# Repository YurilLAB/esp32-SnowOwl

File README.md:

<div align="center">

# 🦉 ESP32-SnowOwl

**A multi-purpose wireless _offensive &amp; defensive_ security multitool.**

Three processors — **ESP32-S3 + ESP32-C5 (5 GHz Wi‑Fi) + ARM Linux** — driving a wall of radios and readers: dual‑band Wi‑Fi, BLE, 2.4 GHz, Sub‑GHz, **LoRa**, IR, **NFC**, **125 kHz RFID**, **iButton** &amp; GPS, in one stackable handheld.

</div>

> ⚠️ **Authorized use only.** SnowOwl is built for security research, education, CTFs, and testing on systems you own or are explicitly authorized to assess. You are solely responsible for complying with all applicable laws and regulations.

---

## 📖 About

**ESP32-SnowOwl** is a hardware evolution of [CiferTech's **ESP32‑DIV**](https://github.com/cifertech/ESP32-DIV) — the open-source ESP32‑S3 wireless multitool. SnowOwl keeps the entire ESP32‑DIV toolset and then piles on the compute, radios and readers the stock board doesn't have.

**Three processors, each doing what it's best at:**

- 🦅 **ESP32‑S3 — the controller.** The base ESP32‑DIV brain: the on‑device UI, 2.4 GHz Wi‑Fi &amp; BLE, and orchestration of every radio.
- 📡 **ESP32‑C5 — the 5 GHz reach.** A dual‑band **Wi‑Fi 6 (2.4 + 5 GHz)** co‑processor that adds the entire **5 GHz** band the S3 can't touch, on its own antenna and its own regulated rail.
- 🐧 **RV1106 ARM Linux — the analyst.** A real Linux computer (Luckfox Core1106) for capture, monitoring, scripting and heavy on‑device tooling — self‑powered from **its own USB‑C**.

Offense on the talons, analysis in the eyes. Silent, patient, built for the dark — the snow owl fits.

---

## 🦉 What SnowOwl adds over ESP32‑DIV

| Addition | Part | What it brings |
|---|---|---|
| 📡 **5 GHz Wi‑Fi co‑processor** | ESP32‑C5‑WROOM‑1U | Dual‑band **Wi‑Fi 6 (2.4 + 5 GHz)** — the 5 GHz band the ESP32‑S3 can't reach. Own U.FL antenna, own AP7361C LDO rail, UART‑linked to the S3. |
| 🐧 **ARM Linux co‑processor** | Luckfox RV1106 (Core1106) | A genuine Linux computer on the shield for capture, monitoring and heavy tooling. Self‑powered from **its own USB‑C**. |
| 🧲 **NFC** (13.56 MHz) | PN532 | Read / emulate / relay over a **dedicated I²C bus** owned by the S3 — independent of the radios. |
| 📇 **125 kHz LF RFID** | HTRC110 + coil | Low‑frequency prox‑card read &amp; emulation (EM4100‑class) — a band the stock board lacks. |
| 🔑 **iButton / 1‑Wire** | 1‑Wire header | Dallas iButton + 1‑Wire contact interface. |
| 📻 **LoRa / long‑range Sub‑GHz** | SX1262 (+ Johanson match) | Long‑range LoRa &amp; FSK on Sub‑GHz, alongside the OOK/ASK radios. |
| 📻 **High‑performance Sub‑GHz** | CC1200 | A higher‑performance Sub‑GHz transceiver in addition to the classic CC1101. |
| 💾 **External flash** | W25Q128 (16 MB) | Non‑volatile storage for captures, logs and dumps. |
| 🧱 **4‑layer, power‑hardened PCB** | — | Dedicated **GND** and **3V3** planes, per‑rail decoupling and bulk caps for clean RF and stable multi‑radio operation. |

---

## 🎯 Features

SnowOwl runs the full **ESP32‑DIV** firmware feature set on the ESP32‑S3, extended with the SnowOwl radios and readers. Capabilities by band:

### 📡 Wi‑Fi — 2.4 GHz (ESP32‑S3) **+ 5 GHz (ESP32‑C5)** · **5 GHz is NEW**
| Capability | Notes |
|---|---|
| Dual‑band recon &amp; scanning | AP / station discovery across **2.4 *and* 5 GHz**, channels, RSSI |
| Deauth / attack testing | Targeted &amp; broadcast frame testing, now on 5 GHz networks too |
| Beacon / probe flooding | SSID beacon spam, probe generation |
| Packet monitor / capture | Sniffing, with hand‑off to the ARM side for storage &amp; analysis |
| Evil‑portal / captive testing | Rogue‑AP and captive‑portal workflows |

### 🔵 Bluetooth / BLE
| Capability | Notes |
|---|---|
| BLE scan &amp; recon | Device discovery, service enumeration |
| Advertising / spam | BLE advertisement flooding &amp; spoofing |
| Proximity‑pairing tests | Device‑spam nuisance testing |

### 📶 2.4 GHz / nRF24 (3× nRF24L01+)
| Capability | Notes |
|---|---|
| Channel scanner / analyzer | 2.4 GHz spectrum sweep across three radios |
| Multi‑channel jamming (test) | Wide/targeted 2.4 GHz interference testing |

### 📻 Sub‑GHz — CC1101 · CC1200 · **SX1262 LoRa**
| Capability | Notes |
|---|---|
| Scan &amp; frequency analysis | RSSI sweep, signal hunting |
| Capture / replay | Record &amp; re‑transmit OOK/ASK signals |
| **LoRa / long‑range** | SX1262 for LoRa &amp; long‑range FSK |
| Jamming (test) | Sub‑GHz interference testing |

### 📺 Infrared (TSOP1838 RX + IR TX)
| Capability | Notes |
|---|---|
| Receive / decode | Capture IR remotes |
| Send / replay | Transmit stored or brute‑forced codes |

### 🧲 NFC / RFID — 13.56 MHz (PN532)
| Capability | Notes |
|---|---|
| Read / dump | MIFARE‑class tags &amp; UIDs |
| Emulate / relay | Card emulation and relay over the dedicated I²C bus |

### 📇 LF RFID — 125 kHz (HTRC110) &amp; 🔑 iButton · **NEW**
| Capability | Notes |
|---|---|
| 125 kHz read / emulate | EM4100‑class prox cards |
| iButton / 1‑Wire | Dallas contact keys |

### 🛰️ GPS (NEO‑M9N)
| Capability | Notes |
|---|---|
| Location &amp; time | Fix, NMEA, wardriving support |

### 🐧 ARM Linux co‑processor (RV1106) · **NEW**
| Capability | Notes |
|---|---|
| On‑device capture &amp; storage | Long‑running packet/loot capture without a laptop, to the 16 MB flash / SD |
| Monitoring / blue‑team | Run standard Linux security &amp; monitoring tooling on‑device |
| Scripting &amp; automation | Python/shell orchestration of the S3 &amp; C5 radios |

### 🧰 Device &amp; System
| Capability | Notes |
|---|---|
| Display UI | On‑device menu on the ESP32‑DIV TFT |
| Storage | microSD + **16 MB external flash** |
| Settings | Per‑module configuration |

> The exact per‑tool menu is inherited from the ESP32‑DIV firmware — see the [ESP32‑DIV wiki](https://github.com/cifertech/ESP32-DIV/wiki) for the full tool list.

---

## 🔧 Hardware Overview

### 🧠 Compute
- **ESP32‑S3** — application processor, 2.4 GHz Wi‑Fi &amp; BLE, UI (on the main board)
- **ESP32‑C5‑WROOM‑1U** — dual‑band **2.4 / 5 GHz Wi‑Fi 6** co‑processor (U.FL antenna, AP7361C LDO rail, UART link)
- **Luckfox RV1106 (Core1106)** — ARM Linux SoM, self‑powered via its **own USB‑C**

### 📡 Radios
- **3× nRF24L01+** — 2.4 GHz
- **CC1101** + **CC1200** — Sub‑GHz transceivers
- **SX1262** (+ Johanson integrated match) — LoRa / long‑range Sub‑GHz
- **7× SMA** antenna ports + U.FL

### 🧲 Readers &amp; sensors
- **PN532** — 13.56 MHz NFC (dedicated I²C bus, 27.12 MHz)
- **HTRC110** + coil — 125 kHz LF RFID
- **iButton / 1‑Wire** contact interface
- **TSOP1838** IR receiver + IR transmit
- **NEO‑M9N** — GPS

### 🔌 Power, storage &amp; protection
- **W25Q128** — 16 MB SPI flash
- microSD
- **AP7361C‑3.3** LDO (C5 rail), dedicated USB‑C for the ARM SoM
- **USBLC6‑2SC6** USB ESD protection, **SN74LVC2G34** level buffer
- Power hardening: bulk + per‑rail decoupling capacitors

Mates to the main board through the existing 20‑pin stack header; pogo/standoff holes are kept clear for a flat stack.

---

## 🧱 PCB / Manufacturing

- Designed in **KiCad 10**.
- **4‑layer stackup** — `F.Cu (signal) · In1 (GND plane) · In2 (3V3 plane) · B.Cu (signal)` for clean RF return paths and a quiet supply.
- Power‑planned per the datasheets of each part (per‑rail decoupling + bulk); RF nets use integrated matching where the transceiver vendors provide it.
- Intended for standard 4‑layer fabrication (e.g. JLCPCB); the 4‑layer option adds only a few dollars per unit over 2‑layer.

> **Status:** hardware design in active development. Placement and power are complete; signal routing is being finished. Renders and design notes live in [`/hardware`](hardware).

---

## ⚠️ Legal &amp; Responsible Use

SnowOwl is an **offensive *and* defensive** research platform. It is intended **only** for:

- testing systems you **own** or are **explicitly authorized** to assess,
- security education, CTFs, and lab research,
- defensive monitoring and blue‑team work.

Do **not** use it to access, disrupt, or interfere with networks, devices, cards, or systems you do not own or lack permission to test. Radio transmission is regulated — respect your local RF laws and licensed bands. **You** are responsible for how you use this tool.

---

## 📜 License

Released under the **MIT License** — see [`LICENSE`](LICENSE).

SnowOwl is a derivative of **ESP32‑DIV** (© CiferTech, MIT). The original work's terms are honored and its authors are credited below.

---

## 🙌 Credits

- **[CiferTech](https://github.com/cifertech)** — the original [ESP32‑DIV](https://github.com/cifertech/ESP32-DIV) platform and firmware that SnowOwl builds on. 🙏
- **YurilLAB** — SnowOwl hardware: the 5 GHz Wi‑Fi + ARM‑Linux compute, the NFC / 125 kHz RFID / iButton / LoRa additions, power hardening, and the 4‑layer redesign.

---

## 💬 Contributing &amp; Support

Issues, ideas, and pull requests are welcome. If SnowOwl is useful to you, a ⭐ helps.

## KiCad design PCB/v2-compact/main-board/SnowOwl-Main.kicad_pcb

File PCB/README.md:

# 🦉 SnowOwl — PCB

**Clean slate.** All previous CAD — boards, schematics, footprints, floorplan and renders — has
been wiped. The hardware direction is changing and the design is being started over from scratch.

```
PCB/
└── RESEARCH.md    ← component & schematic reference carried over from the old attempt
```

## RESEARCH.md

The only thing kept: the electrical research worth not repeating.

- **System architecture** — which processor owns what, and the SPI-spine approach.
- **Component inventory** — every radio/reader, and which ones are self-contained modules vs.
  chip-down parts that need a crystal and an RF front-end.
- **Power** — the single-USB-C / battery topology, plus **datasheet pinout corrections** for the
  charger, regulators and fuel gauge (the old symbols had invented pinouts).
- **RF front-end topologies** — matching + filter chains for the chip-down radios, with the
  caveat that every L/C value still needs VNA tuning.
- **Schematic gotchas** — including the net-merge bug that silently shorted whole nets twice.

It deliberately assumes **no particular board size, layout or form factor**, so none of it
constrains the new design.

> Fabrication outputs (`gerbers-out/`, zips) are git-ignored.

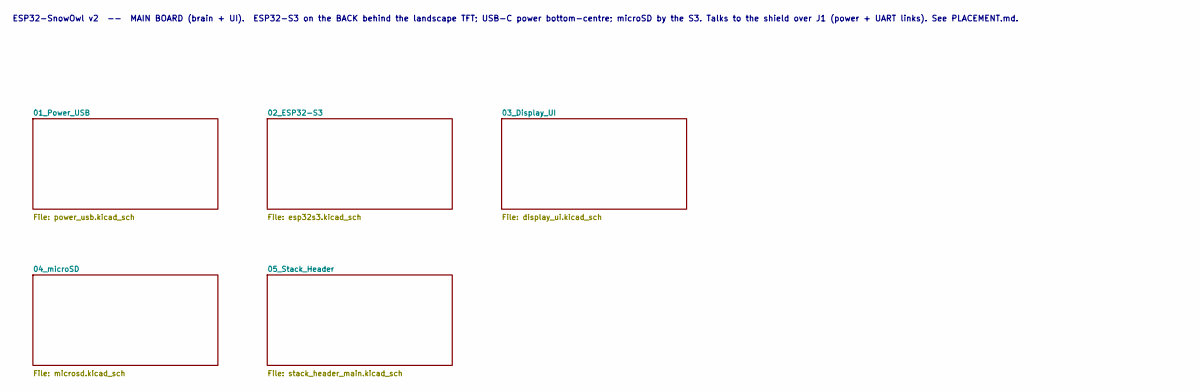
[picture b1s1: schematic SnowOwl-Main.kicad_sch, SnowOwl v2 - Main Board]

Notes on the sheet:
ESP32-SnowOwl v2 -- MAIN BOARD (brain + UI). ESP32-S3 on the BACK behind the landscape TFT; USB-C power bottom-centre; microSD by the S3. Talks to the shield over J1 (power + UART links). See PLACEMENT.md.

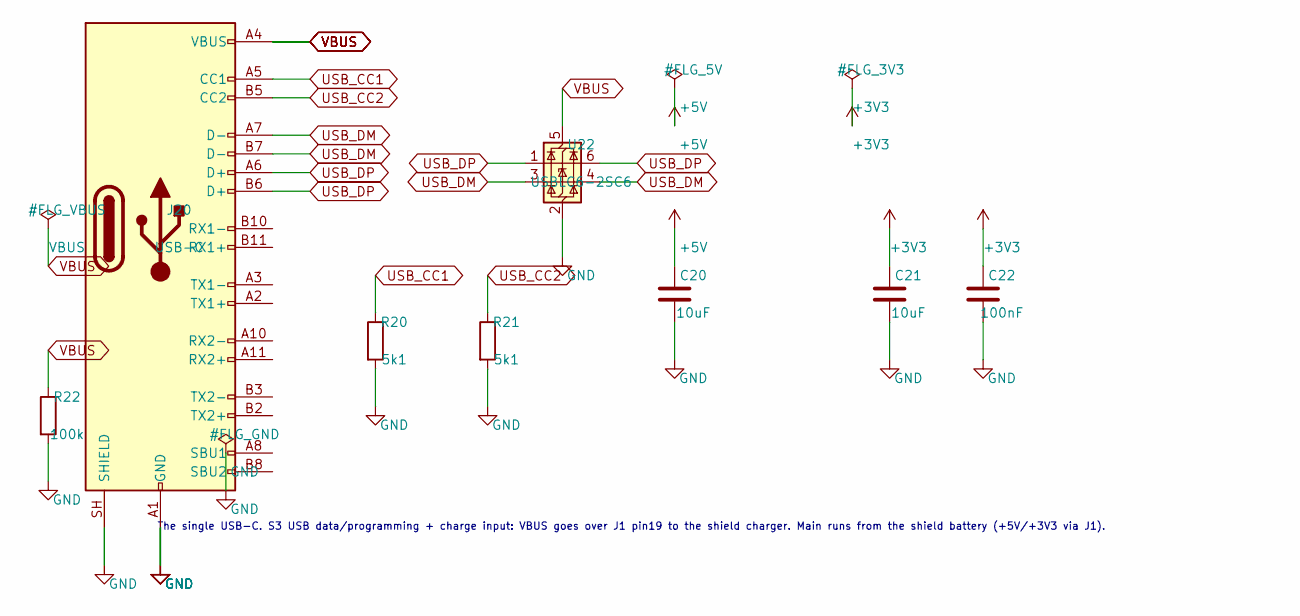
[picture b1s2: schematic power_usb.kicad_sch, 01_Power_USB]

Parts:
C20, C21: 10uF; C_0402_1005Metric
C22: 100nF; C_0402_1005Metric
J20: USB-C; USB_C_Receptacle_HRO_TYPE-C-31-M-12
R20, R21: 5k1; R_0402_1005Metric
R22: 100k; R_0402_1005Metric
U22: USBLC6-2SC6; SOT-23-6

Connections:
+3V3: C21.1, C22.1; also elsewhere on the board
+5V: C20.1; also elsewhere on the board
GND: C20.2, C21.2, C22.2, J20.A1 (GND), J20.A12 (GND), J20.B1 (GND), J20.B12 (GND), J20.SH (SHIELD), R20.2, R21.2, R22.2, U22.2 (GND); also elsewhere on the board
USB_CC1: J20.A5 (CC1), R20.1
USB_CC2: J20.B5 (CC2), R21.1
USB_DM: J20.A7 (D-), J20.B7 (D-), U22.3 (I/O2), U22.4 (I/O2); also elsewhere on the board
USB_DP: J20.A6 (D+), J20.B6 (D+), U22.1 (I/O1), U22.6 (I/O1); also elsewhere on the board
VBUS: J20.A4 (VBUS), J20.A9 (VBUS), J20.B4 (VBUS), J20.B9 (VBUS), R22.1, U22.5 (VBUS); also elsewhere on the board

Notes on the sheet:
The single USB-C. S3 USB data/programming + charge input: VBUS goes over J1 pin19 to the shield charger. Main runs from the shield battery (+5V/+3V3 via J1).

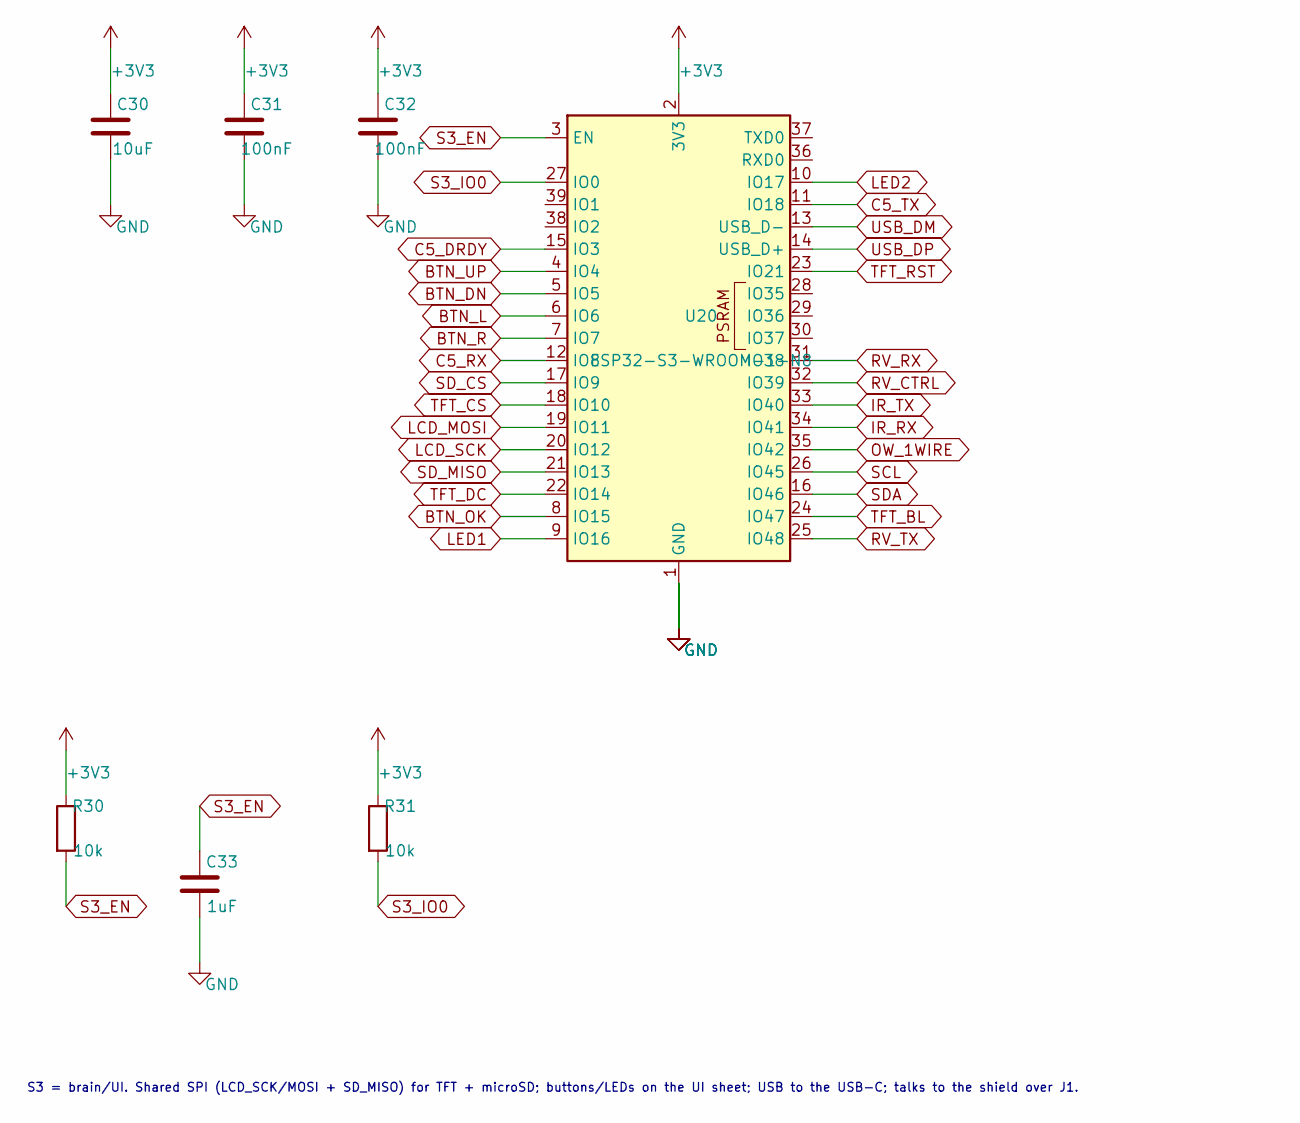
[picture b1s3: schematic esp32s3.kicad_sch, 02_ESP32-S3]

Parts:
C30: 10uF; C_0402_1005Metric
C31, C32: 100nF; C_0402_1005Metric
C33: 1uF; C_0402_1005Metric
R30, R31: 10k; R_0402_1005Metric
U20: ESP32-S3-WROOM-1-N8; ESP32-S3-WROOM-1

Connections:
+3V3: C30.1, C31.1, C32.1, R30.1, R31.1, U20.2 (3V3); also elsewhere on the board
BTN_DN: U20.5 (IO5); also elsewhere on the board
BTN_L: U20.6 (IO6); also elsewhere on the board
BTN_OK: U20.8 (IO15); also elsewhere on the board
BTN_R: U20.7 (IO7); also elsewhere on the board
BTN_UP: U20.4 (IO4); also elsewhere on the board
C5_DRDY: U20.15 (IO3); also elsewhere on the board
C5_RX: U20.12 (IO8); also elsewhere on the board
C5_TX: U20.11 (IO18); also elsewhere on the board
GND: C30.2, C31.2, C32.2, C33.2, U20.1 (GND), U20.40 (GND), U20.41 (GND); also elsewhere on the board
IR_RX: U20.34 (IO41); also elsewhere on the board
IR_TX: U20.33 (IO40); also elsewhere on the board
LCD_MOSI: U20.19 (IO11); also elsewhere on the board
LCD_SCK: U20.20 (IO12); also elsewhere on the board
LED1: U20.9 (IO16); also elsewhere on the board
LED2: U20.10 (IO17); also elsewhere on the board
OW_1WIRE: U20.35 (IO42); also elsewhere on the board
RV_CTRL: U20.32 (IO39); also elsewhere on the board
RV_RX: U20.31 (IO38); also elsewhere on the board
RV_TX: U20.25 (IO48); also elsewhere on the board
S3_EN: C33.1, R30.2, U20.3 (EN)
S3_IO0: R31.2, U20.27 (IO0)
SCL: U20.26 (IO45); also elsewhere on the board
SDA: U20.16 (IO46); also elsewhere on the board
SD_CS: U20.17 (IO9); also elsewhere on the board
SD_MISO: U20.21 (IO13); also elsewhere on the board
TFT_BL: U20.24 (IO47); also elsewhere on the board
TFT_CS: U20.18 (IO10); also elsewhere on the board
TFT_DC: U20.22 (IO14); also elsewhere on the board
TFT_RST: U20.23 (IO21); also elsewhere on the board
USB_DM: U20.13 (USB_D-); also elsewhere on the board
USB_DP: U20.14 (USB_D+); also elsewhere on the board

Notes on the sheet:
S3 = brain/UI. Shared SPI (LCD_SCK/MOSI + SD_MISO) for TFT + microSD; buttons/LEDs on the UI sheet; USB to the USB-C; talks to the shield over J1.

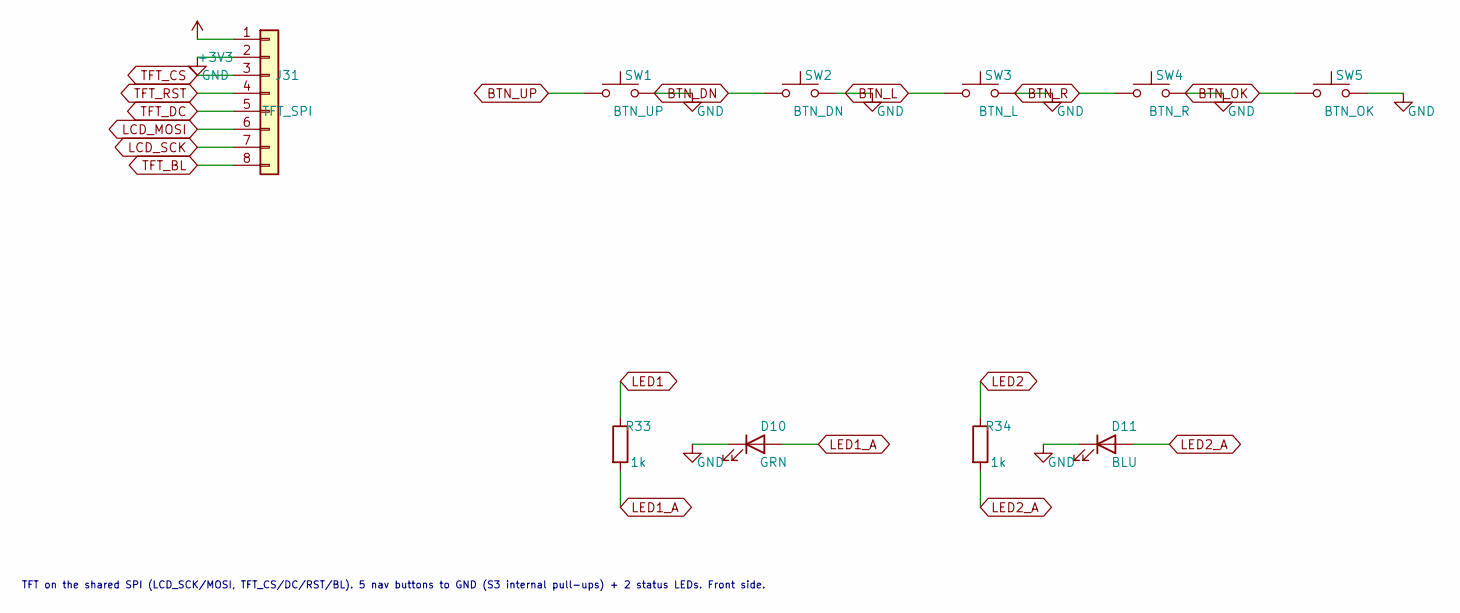
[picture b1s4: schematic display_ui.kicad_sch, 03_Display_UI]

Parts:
D10: GRN; LED_0805_2012Metric
D11: BLU; LED_0805_2012Metric
J31: TFT_SPI; PinHeader_1x08_P2.54mm_Vertical
R33, R34: 1k; R_0402_1005Metric
SW1: BTN_UP; SW_PUSH_6mm
SW2: BTN_DN; SW_PUSH_6mm
SW3: BTN_L; SW_PUSH_6mm
SW4: BTN_R; SW_PUSH_6mm
SW5: BTN_OK; SW_PUSH_6mm

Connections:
+3V3: J31.1; also elsewhere on the board
BTN_DN: SW2.1; also elsewhere on the board
BTN_L: SW3.1; also elsewhere on the board
BTN_OK: SW5.1; also elsewhere on the board
BTN_R: SW4.1; also elsewhere on the board
BTN_UP: SW1.1; also elsewhere on the board
GND: D10.1 (K), D11.1 (K), J31.2, SW1.2, SW2.2, SW3.2, SW4.2, SW5.2; also elsewhere on the board
LCD_MOSI: J31.6; also elsewhere on the board
LCD_SCK: J31.7; also elsewhere on the board
LED1: R33.1; also elsewhere on the board
LED1_A: D10.2 (A), R33.2
LED2: R34.1; also elsewhere on the board
LED2_A: D11.2 (A), R34.2
TFT_BL: J31.8; also elsewhere on the board
TFT_CS: J31.3; also elsewhere on the board
TFT_DC: J31.5; also elsewhere on the board
TFT_RST: J31.4; also elsewhere on the board

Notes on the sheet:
TFT on the shared SPI (LCD_SCK/MOSI, TFT_CS/DC/RST/BL). 5 nav buttons to GND (S3 internal pull-ups) + 2 status LEDs. Front side.

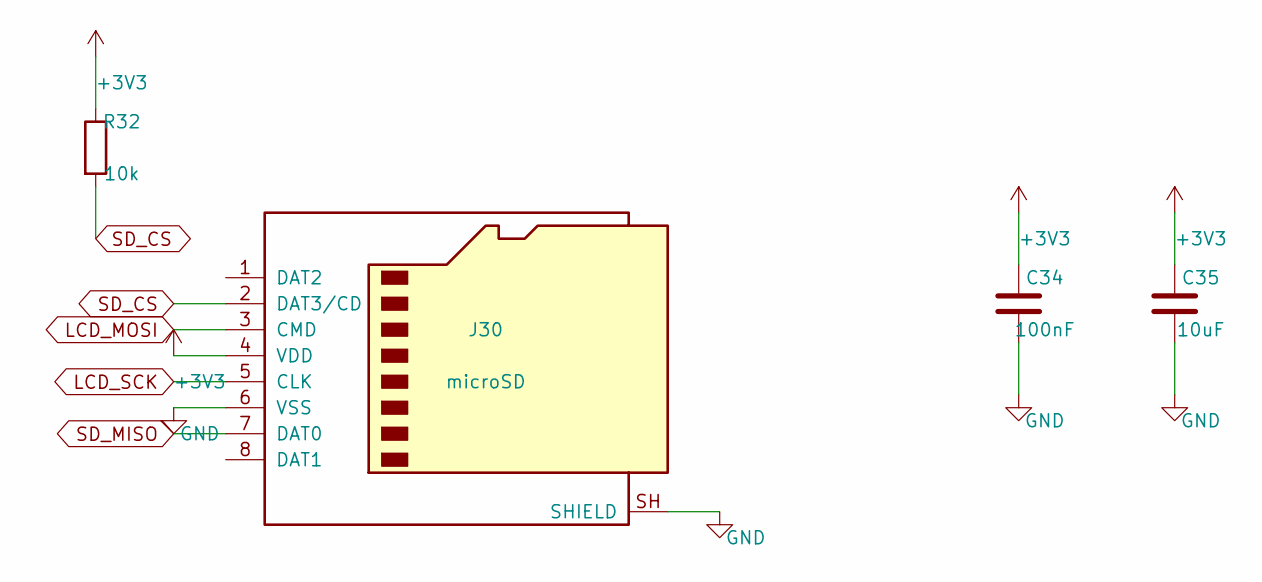
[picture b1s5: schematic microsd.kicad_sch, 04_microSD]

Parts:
C34: 100nF; C_0402_1005Metric
C35: 10uF; C_0402_1005Metric
J30: microSD; microSD_HC_Hirose_DM3AT-SF-PEJM5
R32: 10k; R_0402_1005Metric

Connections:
+3V3: C34.1, C35.1, J30.4 (VDD), R32.1; also elsewhere on the board
GND: C34.2, C35.2, J30.6 (VSS), J30.SH (SHIELD); also elsewhere on the board
LCD_MOSI: J30.3 (CMD); also elsewhere on the board
LCD_SCK: J30.5 (CLK); also elsewhere on the board
SD_CS: J30.2 (DAT3/CD), R32.2; also elsewhere on the board
SD_MISO: J30.7 (DAT0); also elsewhere on the board

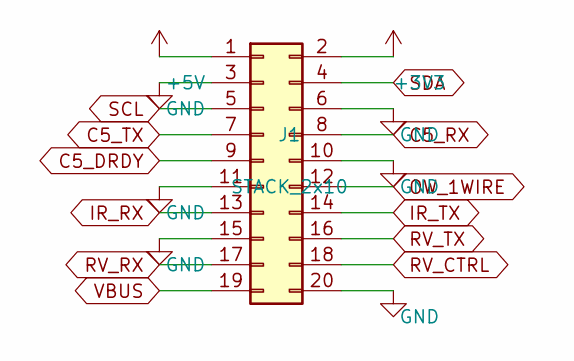
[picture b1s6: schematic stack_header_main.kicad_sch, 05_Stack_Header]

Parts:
J1: STACK_2x10; StackHeader_2x10

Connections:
+3V3: J1.2; also elsewhere on the board
+5V: J1.1; also elsewhere on the board
C5_DRDY: J1.9; also elsewhere on the board
C5_RX: J1.8; also elsewhere on the board
C5_TX: J1.7; also elsewhere on the board
GND: J1.3, J1.6, J1.10, J1.11, J1.15, J1.20; also elsewhere on the board
IR_RX: J1.13; also elsewhere on the board
IR_TX: J1.14; also elsewhere on the board
OW_1WIRE: J1.12; also elsewhere on the board
RV_CTRL: J1.18; also elsewhere on the board
RV_RX: J1.17; also elsewhere on the board
RV_TX: J1.16; also elsewhere on the board
SCL: J1.5; also elsewhere on the board
SDA: J1.4; also elsewhere on the board
VBUS: J1.19; also elsewhere on the board

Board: 4 copper layers, 29 parts (18 on the bottom side), 38 nets, no tracks yet.

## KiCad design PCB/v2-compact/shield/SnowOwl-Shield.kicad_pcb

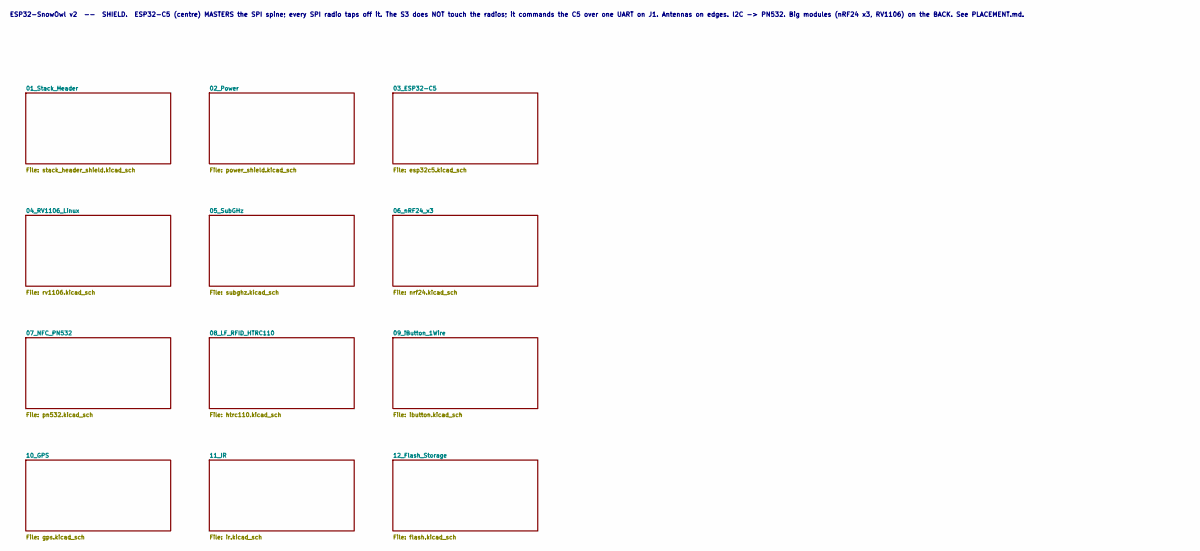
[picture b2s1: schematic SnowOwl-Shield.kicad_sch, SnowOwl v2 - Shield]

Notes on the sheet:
ESP32-SnowOwl v2 -- SHIELD. ESP32-C5 (centre) MASTERS the SPI spine; every SPI radio taps off it. The S3 does NOT touch the radios; it commands the C5 over one UART on J1. Antennas on edges. I2C -> PN532. Big modules (nRF24 x3, RV1106) on the BACK. See PLACEMENT.md.

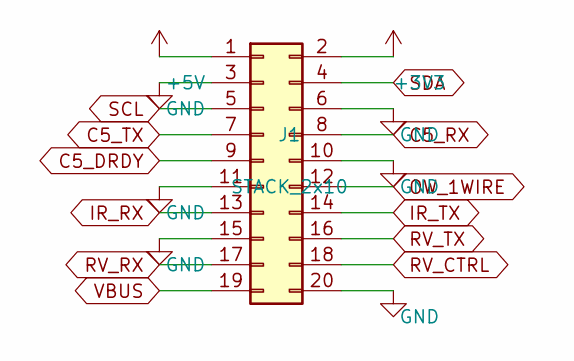
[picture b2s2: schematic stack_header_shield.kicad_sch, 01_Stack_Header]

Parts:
J1: STACK_2x10; StackHeader_2x10

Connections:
+3V3: J1.2; also elsewhere on the board
C5_DRDY: J1.9; also elsewhere on the board
C5_RX: J1.8; also elsewhere on the board
C5_TX: J1.7; also elsewhere on the board
IR_RX: J1.13; also elsewhere on the board
IR_TX: J1.14; also elsewhere on the board
OW_1WIRE: J1.12; also elsewhere on the board
RV_CTRL: J1.18; also elsewhere on the board
RV_RX: J1.17; also elsewhere on the board
RV_TX: J1.16; also elsewhere on the board
SCL: J1.5; also elsewhere on the board
SDA: J1.4; also elsewhere on the board
VBUS: J1.19; also elsewhere on the board

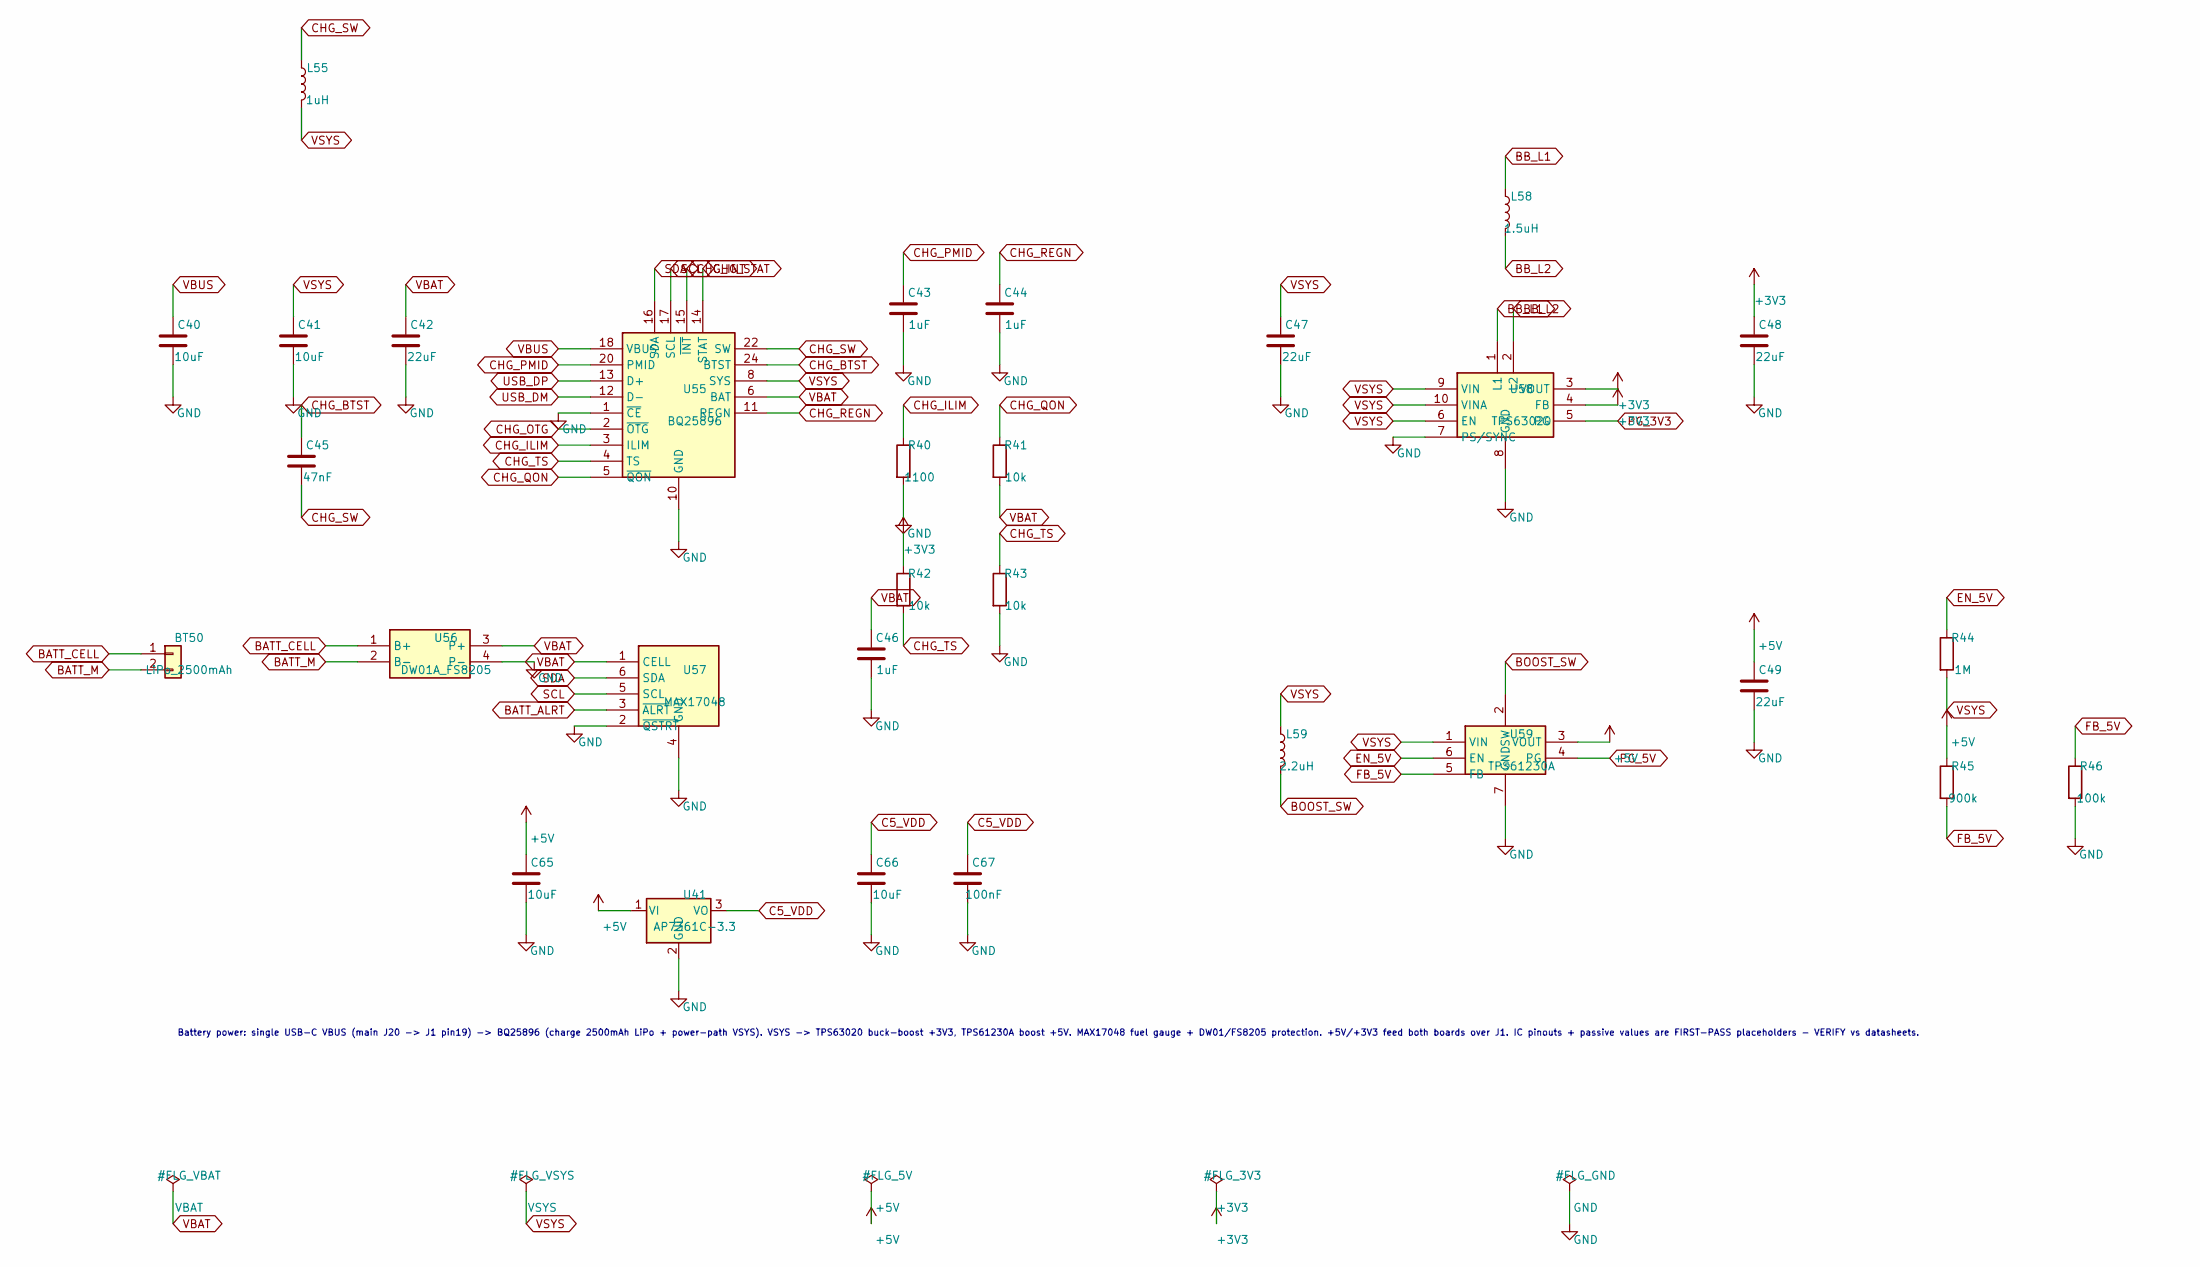
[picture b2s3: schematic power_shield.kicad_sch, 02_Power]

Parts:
BT50: LiPo_2500mAh; JST_PH_S2B-PH-K_1x02_P2.00mm_Horizontal
C40, C41, C65, C66: 10uF; C_0402_1005Metric
C42, C47, C48, C49: 22uF; C_0402_1005Metric
C43, C44, C46: 1uF; C_0402_1005Metric
C45: 47nF; C_0402_1005Metric
C67: 100nF; C_0402_1005Metric
L55: 1uH; L_1210_3225Metric
L58: 1.5uH; L_1210_3225Metric
L59: 2.2uH; L_1210_3225Metric
R40: 1100; R_0402_1005Metric
R41, R42, R43: 10k; R_0402_1005Metric
R44: 1M; R_0402_1005Metric
R45: 900k; R_0402_1005Metric
R46: 100k; R_0402_1005Metric
U41: AP7361C-3.3; SOT-23-5
U55: BQ25896; QFN-24-1EP_4x4mm_P0.5mm_EP2.5x2.5mm
U56: DW01A_FS8205; SOT-23-6
U57: MAX17048; DFN-8-1EP_2x3mm_P0.5mm_EP0.61x2.2mm
U58: TPS63020; DFN-10-1EP_3x3mm_P0.5mm_EP1.58x2.35mm
U59: TPS61230A; DFN-10-1EP_3x3mm_P0.5mm_EP1.58x2.35mm

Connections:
+3V3: C48.1, R42.1, U58.3 (VOUT), U58.4 (FB); also elsewhere on the board
BATT_ALRT: U57.3 (~ALRT)
BATT_CELL: BT50.1, U56.1 (B+)
BATT_M: BT50.2, U56.2 (B-)
BB_L1: L58.1, U58.1 (L1)
BB_L2: L58.2, U58.2 (L2)
BOOST_SW: L59.2, U59.2 (SW)
C5_VDD: C66.1, C67.1, U41.3 (VO); also elsewhere on the board
CHG_BTST: C45.1, U55.24 (BTST)
CHG_ILIM: R40.1, U55.3 (ILIM)
CHG_INT: U55.15 (~INT)
CHG_OTG: U55.2 (~OTG)
CHG_PMID: C43.1, U55.20 (PMID)
CHG_QON: R41.1, U55.5 (~QON)
CHG_REGN: C44.1, U55.11 (REGN)
CHG_STAT: U55.14 (STAT)
CHG_SW: C45.2, L55.1, U55.22 (SW)
CHG_TS: R42.2, R43.1, U55.4 (TS)
EN_5V: R44.1, U59.6 (EN)
FB_5V: R45.2, R46.1, U59.5 (FB)
PG_3V3: U58.5 (PG)
PG_5V: U59.4 (PG)
SCL: U55.17 (SCL), U57.5 (SCL); also elsewhere on the board
SDA: U55.16 (SDA), U57.6 (SDA); also elsewhere on the board
USB_DM: U55.12 (D-)
USB_DP: U55.13 (D+)
VBAT: C42.1, C46.1, R41.2, U55.6 (BAT), U56.3 (P+), U57.1 (CELL)
VBUS: C40.1, U55.18 (VBUS); also elsewhere on the board
VSYS: C41.1, C47.1, L55.2, L59.1, R44.2, U55.8 (SYS), U58.6 (EN), U58.9 (VIN), U58.10 (VINA), U59.1 (VIN)

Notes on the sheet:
Battery power: single USB-C VBUS (main J20 -> J1 pin19) -> BQ25896 (charge 2500mAh LiPo + power-path VSYS). VSYS -> TPS63020 buck-boost +3V3, TPS61230A boost +5V. MAX17048 fuel gauge + DW01/FS8205 protection. +5V/+3V3 feed both boards over J1. IC pinouts + passive values are FIRST-PASS placeholders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

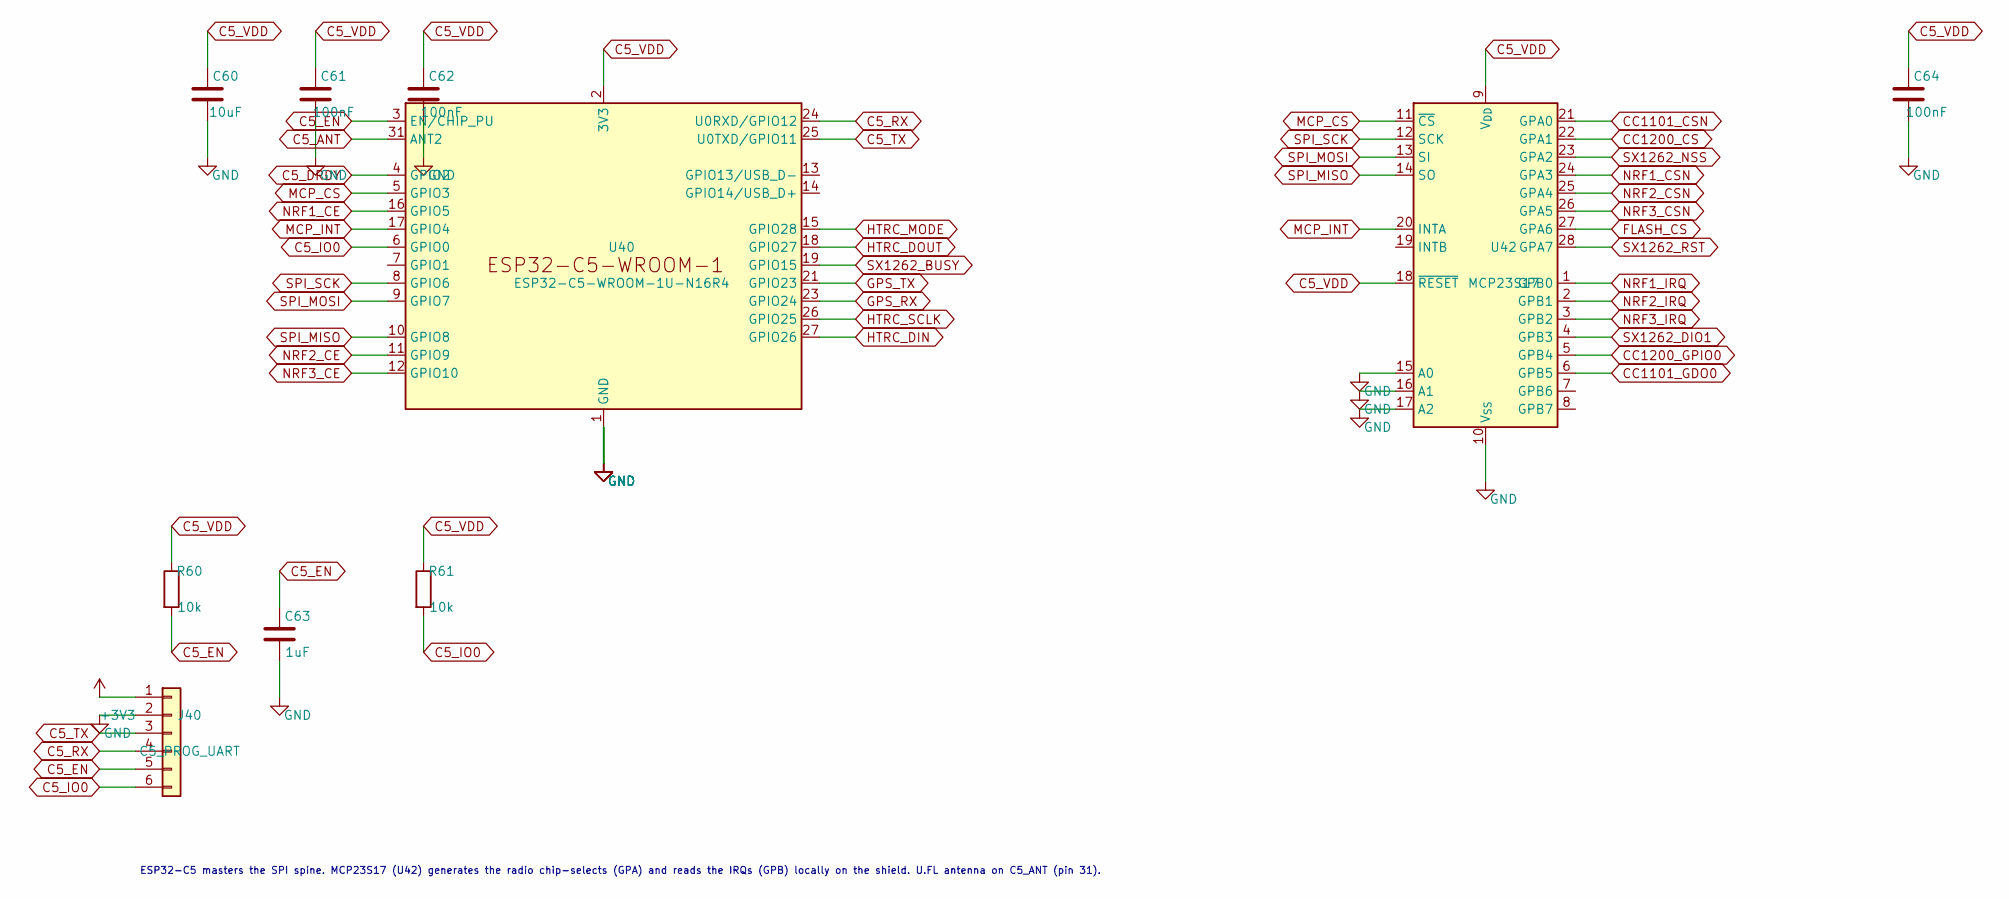
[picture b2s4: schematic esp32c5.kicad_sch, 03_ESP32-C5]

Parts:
C60: 10uF; C_0402_1005Metric
C61, C62, C64: 100nF; C_0402_1005Metric
C63: 1uF; C_0402_1005Metric
J40: C5_PROG_UART; PinHeader_1x06_P2.54mm_Vertical
R60, R61: 10k; R_0402_1005Metric
U40: ESP32-C5-WROOM-1U-N16R4; ESP32-C5-WROOM-1U
U42: MCP23S17; SOIC-28W_7.5x17.9mm_P1.27mm

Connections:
+3V3: J40.1; also elsewhere on the board
C5_ANT: U40.31 (ANT2)
C5_DRDY: U40.4 (GPIO2); also elsewhere on the board
C5_EN: C63.1, J40.5, R60.2, U40.3 (EN/CHIP_PU)
C5_IO0: J40.6, R61.2, U40.6 (GPIO0)
C5_RX: J40.4, U40.24 (U0RXD/GPIO12); also elsewhere on the board
C5_TX: J40.3, U40.25 (U0TXD/GPIO11); also elsewhere on the board
C5_VDD: C60.1, C61.1, C62.1, C64.1, R60.1, R61.1, U40.2 (3V3), U42.9 (V_{DD}), U42.18 (~RESET); also elsewhere on the board
CC1101_CSN: U42.21 (GPA0); also elsewhere on the board
CC1101_GDO0: U42.6 (GPB5); also elsewhere on the board
CC1200_CS: U42.22 (GPA1); also elsewhere on the board
CC1200_GPIO0: U42.5 (GPB4); also elsewhere on the board
FLASH_CS: U42.27 (GPA6); also elsewhere on the board
GPS_RX: U40.23 (GPIO24); also elsewhere on the board
GPS_TX: U40.21 (GPIO23); also elsewhere on the board
HTRC_DIN: U40.27 (GPIO26); also elsewhere on the board
HTRC_DOUT: U40.18 (GPIO27); also elsewhere on the board
HTRC_MODE: U40.15 (GPIO28); also elsewhere on the board
HTRC_SCLK: U40.26 (GPIO25); also elsewhere on the board
MCP_CS: U40.5 (GPIO3), U42.11 (~CS)
MCP_INT: U40.17 (GPIO4), U42.20 (INTA)
NRF1_CE: U40.16 (GPIO5); also elsewhere on the board
NRF1_CSN: U42.24 (GPA3); also elsewhere on the board
NRF1_IRQ: U42.1 (GPB0); also elsewhere on the board
NRF2_CE: U40.11 (GPIO9); also elsewhere on the board
NRF2_CSN: U42.25 (GPA4); also elsewhere on the board
NRF2_IRQ: U42.2 (GPB1); also elsewhere on the board
NRF3_CE: U40.12 (GPIO10); also elsewhere on the board
NRF3_CSN: U42.26 (GPA5); also elsewhere on the board
NRF3_IRQ: U42.3 (GPB2); also elsewhere on the board
SPI_MISO: U40.10 (GPIO8), U42.14 (SO); also elsewhere on the board
SPI_MOSI: U40.9 (GPIO7), U42.13 (SI); also elsewhere on the board
SPI_SCK: U40.8 (GPIO6), U42.12 (SCK); also elsewhere on the board
SX1262_BUSY: U40.19 (GPIO15); also elsewhere on the board
SX1262_DIO1: U42.4 (GPB3); also elsewhere on the board
SX1262_NSS: U42.23 (GPA2); also elsewhere on the board
SX1262_RST: U42.28 (GPA7); also elsewhere on the board

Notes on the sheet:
ESP32-C5 masters the SPI spine. MCP23S17 (U42) generates the radio chip-selects (GPA) and reads the IRQs (GPB) locally on the shield. U.FL antenna on C5_ANT (pin 31).

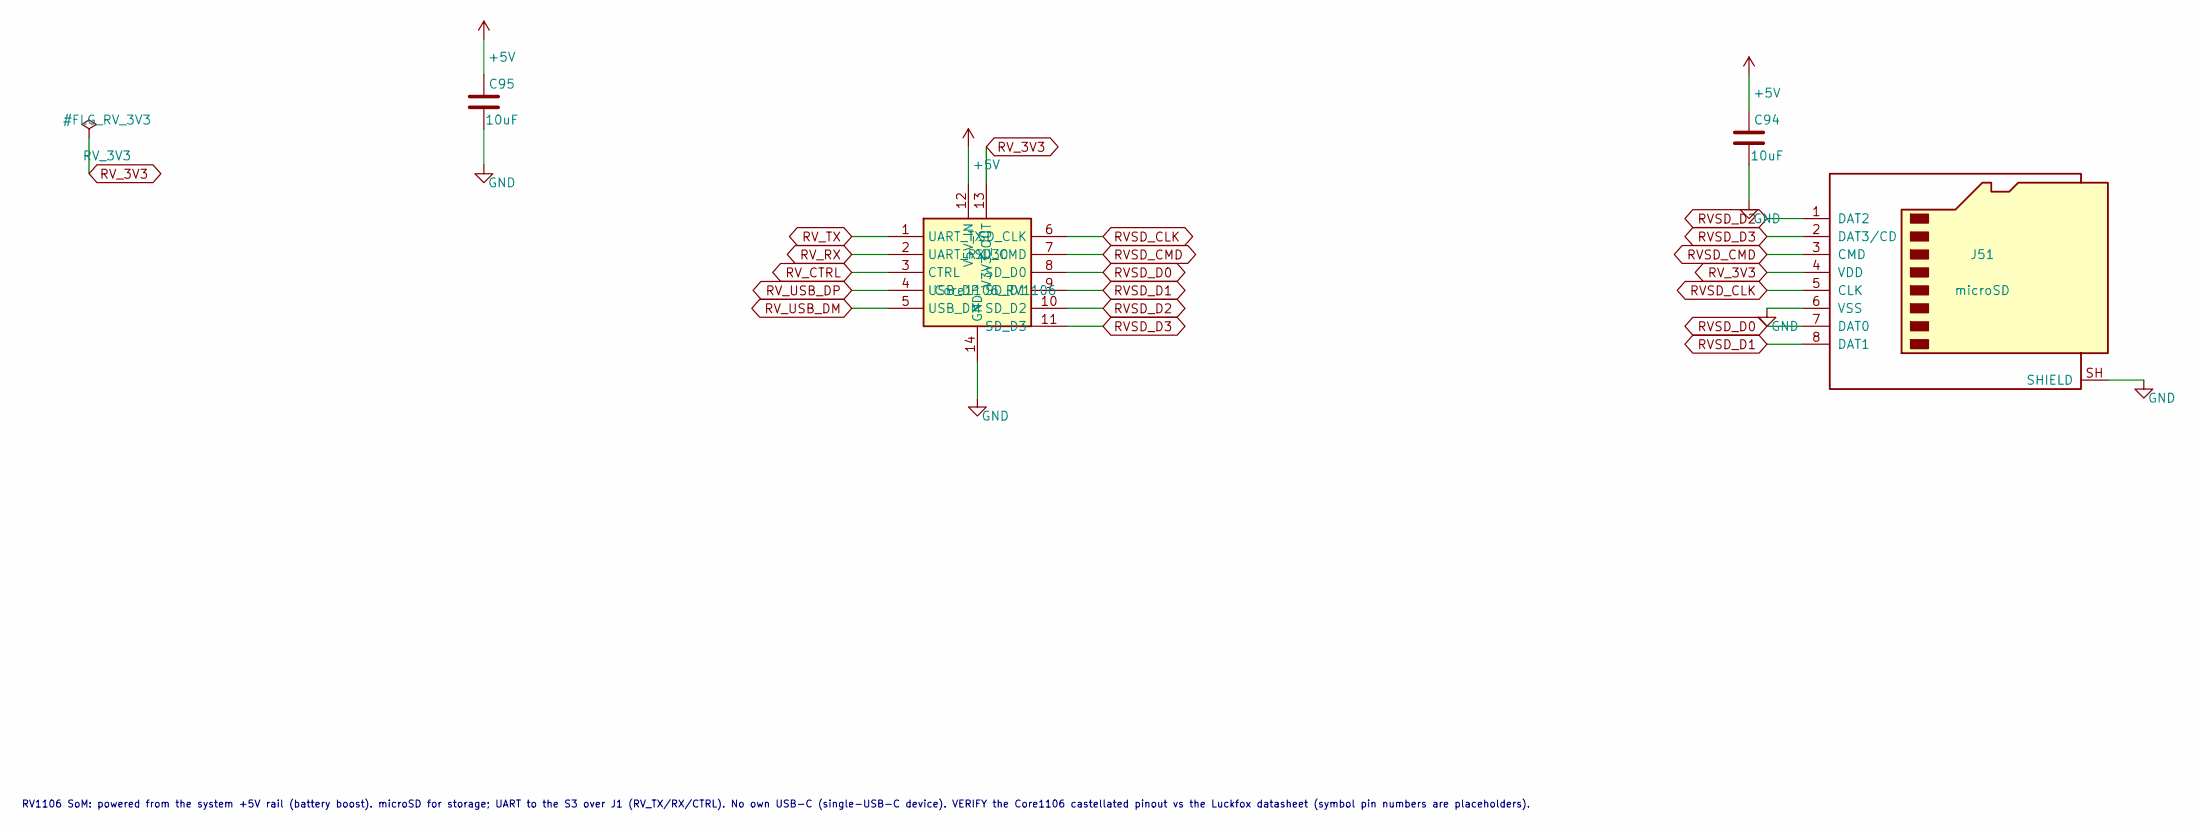
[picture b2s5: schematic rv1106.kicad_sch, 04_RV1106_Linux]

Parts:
C94, C95: 10uF; C_0402_1005Metric
J51: microSD; microSD_HC_Hirose_DM3AT-SF-PEJM5
U30: Core1106_RV1106; RV1106_Core1106

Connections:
RVSD_CLK: J51.5 (CLK), U30.6 (SD_CLK)
RVSD_CMD: J51.3 (CMD), U30.7 (SD_CMD)
RVSD_D0: J51.7 (DAT0), U30.8 (SD_D0)
RVSD_D1: J51.8 (DAT1), U30.9 (SD_D1)
RVSD_D2: J51.1 (DAT2), U30.10 (SD_D2)
RVSD_D3: J51.2 (DAT3/CD), U30.11 (SD_D3)
RV_3V3: J51.4 (VDD), U30.13 (V3V3_OUT)
RV_CTRL: U30.3 (CTRL); also elsewhere on the board
RV_RX: U30.2 (UART_RX); also elsewhere on the board
RV_TX: U30.1 (UART_TX); also elsewhere on the board
RV_USB_DM: U30.5 (USB_DM)
RV_USB_DP: U30.4 (USB_DP)

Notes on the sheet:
RV1106 SoM: powered from the system +5V rail (battery boost). microSD for storage; UART to the S3 over J1 (RV_TX/RX/CTRL). No own USB-C (single-USB-C device). VERIFY the Core1106 castellated pinout vs the Luckfox datasheet (symbol pin numbers are placeholders).

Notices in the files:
README.md:
License: MIT
